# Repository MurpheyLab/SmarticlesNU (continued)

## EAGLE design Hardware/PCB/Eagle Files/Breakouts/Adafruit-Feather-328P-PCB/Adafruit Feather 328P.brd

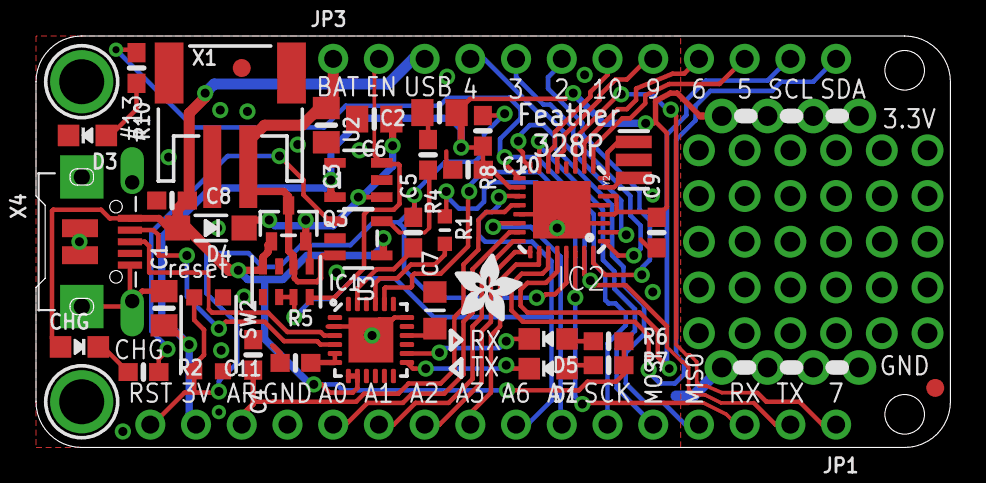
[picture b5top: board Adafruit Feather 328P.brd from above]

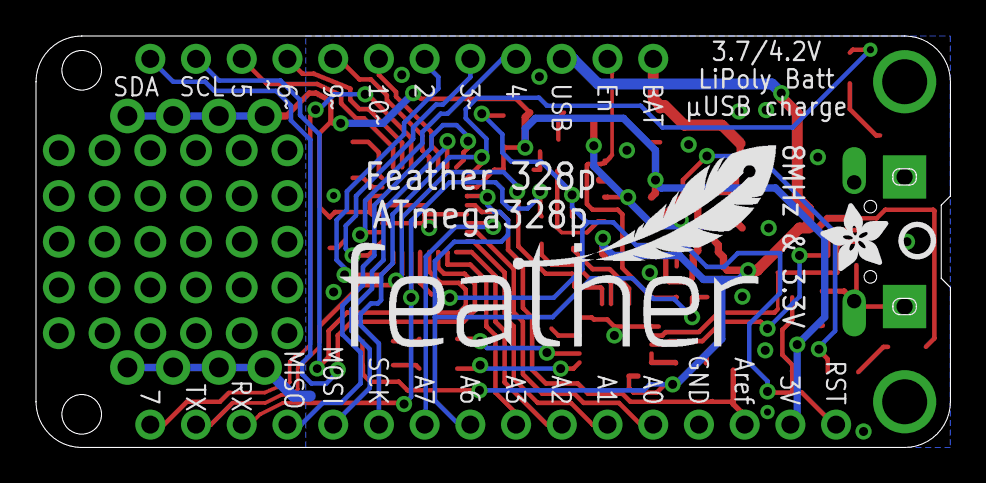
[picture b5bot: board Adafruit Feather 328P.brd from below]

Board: 2 copper layers, 50.8 x 22.9 mm, 43 parts (3 on the bottom side), 45 nets.

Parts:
C1, C2: 10uF; 0805-NO
C3, C6: 10µF; 0805-NO
C4, C5, C9, C10: 0.1uF; 0603-NO
C7: 10uF; _0805MP
C8, C11: 1uF; 0603-NO
CHG: ORANGE; CHIPLED_0805_NOOUTLINE
D1, D5: YELLOW; CHIPLED_0805_NOOUTLINE
D3: RED; CHIPLED_0805_NOOUTLINE
D4: MBR120; SOD-123
IC1: CP2104; QFN24_4MM_SMSC
IC2: ATMEGA328P; MLF32-TH
JP1: 1X16_ROUND
JP3: 1X12_ROUND
Q3: DMG341; SOT23-R
R1: 1K; _0603MP
R2, R6, R7, R10: 1K; 0603-NO
R4, R8: 10K; 0603-NO
R5: 100K; RESPACK_4X0603
SW2: KMR2; BTN_KMR2_4.6X2.8
U2: AP2112-3.3; SOT23-5
U3: MCP73831T-2ACI/OT; SOT23-5
U$9: FEATHERLOGO
U$13: PCBFEAT-REV-040
U$15, U$44: ADAFRUIT_3.5MM
U$31, U$32: MOUNTINGHOLE2.5; MOUNTINGHOLE_2.5_PLATED
U$34, U$35: FIDUCIAL_1MM
X1: JSTPH; JSTPH2
X4: 20329; 4UCONN_20329_V2
Y2: CSTCE16M0V53-R0 8MHZ; RESONATOR

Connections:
3.3V: C1.1, C2.1, C9.2, C10.2, IC2.4, IC2.6, IC2.18, JP1.15, R8.2, U2.5
A0: IC2.23, JP1.12
A1: IC2.24, JP1.11
A2: IC2.25, JP1.10
A3: IC2.26, JP1.9
A4/SDA: IC2.27, JP3.12
A5/SCL: IC2.28, JP3.11
A6: IC2.19, JP1.8, R5.6, R5.7
A7: IC2.22, JP1.7
AREF: C4.2, IC2.20, JP1.14
D0/RX: IC2.30, JP1.3, R1.1
D1/TX: IC1.20, IC2.31, JP1.2
D2: IC2.32, JP3.6
D3: IC2.1, JP3.5
D4: IC2.2, JP3.4
D5: IC2.9, JP3.10
D6: IC2.10, JP3.9
D7: IC2.11, JP1.1
D9: IC2.13, JP3.8
D10: IC2.14, JP3.7
D11/MOSI: IC2.15, JP1.5
D12/MISO: IC2.16, JP1.4
D13/SCK: IC2.17, JP1.6, R10.1
DTR: C5.1, IC1.23
EN: JP3.2, R5.8, U2.3
GND: C1.2, C2.2, C3.2, C4.1, C6.2, C7.2, C8.1, C9.1, C10.1, C11.2, D3.C, IC1.2, IC1.18, IC1.THERM, IC2.3, IC2.5, IC2.21, IC2.TH, JP1.13, R4.1, R5.3, R5.5, SW2.A, SW2.A', U2.2, U3.2, X1.1, X4.BASE@1, X4.BASE@2, X4.GND, X4.SPRT@1, X4.SPRT@2, X4.SPRT@3, X4.SPRT@4, Y2.2
unnamed: CHG.C, R2.1
unnamed: IC1.3, X4.D+
unnamed: R2.2, U3.1
unnamed: R4.2, U3.5
unnamed: D3.A, R10.2
unnamed: IC1.4, X4.D-
unnamed: C6.1, D4.C, Q3.2, R5.1, U2.1
unnamed: D1.A, R7.1
unnamed: D5.A, R6.1
unnamed: C11.1, IC1.5, IC1.6
unnamed: C7.1, IC1.16
RESET: C5.2, IC2.29, JP1.16, R8.1, SW2.B, SW2.B'
RXD: IC1.21, R1.2
RXLED: D1.C, IC1.13
TXLED: D5.C, IC1.14
VBAT: C3.1, JP3.1, Q3.3, R5.2, U3.3, X1.2
VBUS: C8.2, CHG.A, D4.A, IC1.7, IC1.8, JP3.3, Q3.1, R5.4, R6.2, R7.2, U3.4, X4.VBUS
XTAL1: IC2.8, Y2.3
XTAL2: IC2.7, Y2.1

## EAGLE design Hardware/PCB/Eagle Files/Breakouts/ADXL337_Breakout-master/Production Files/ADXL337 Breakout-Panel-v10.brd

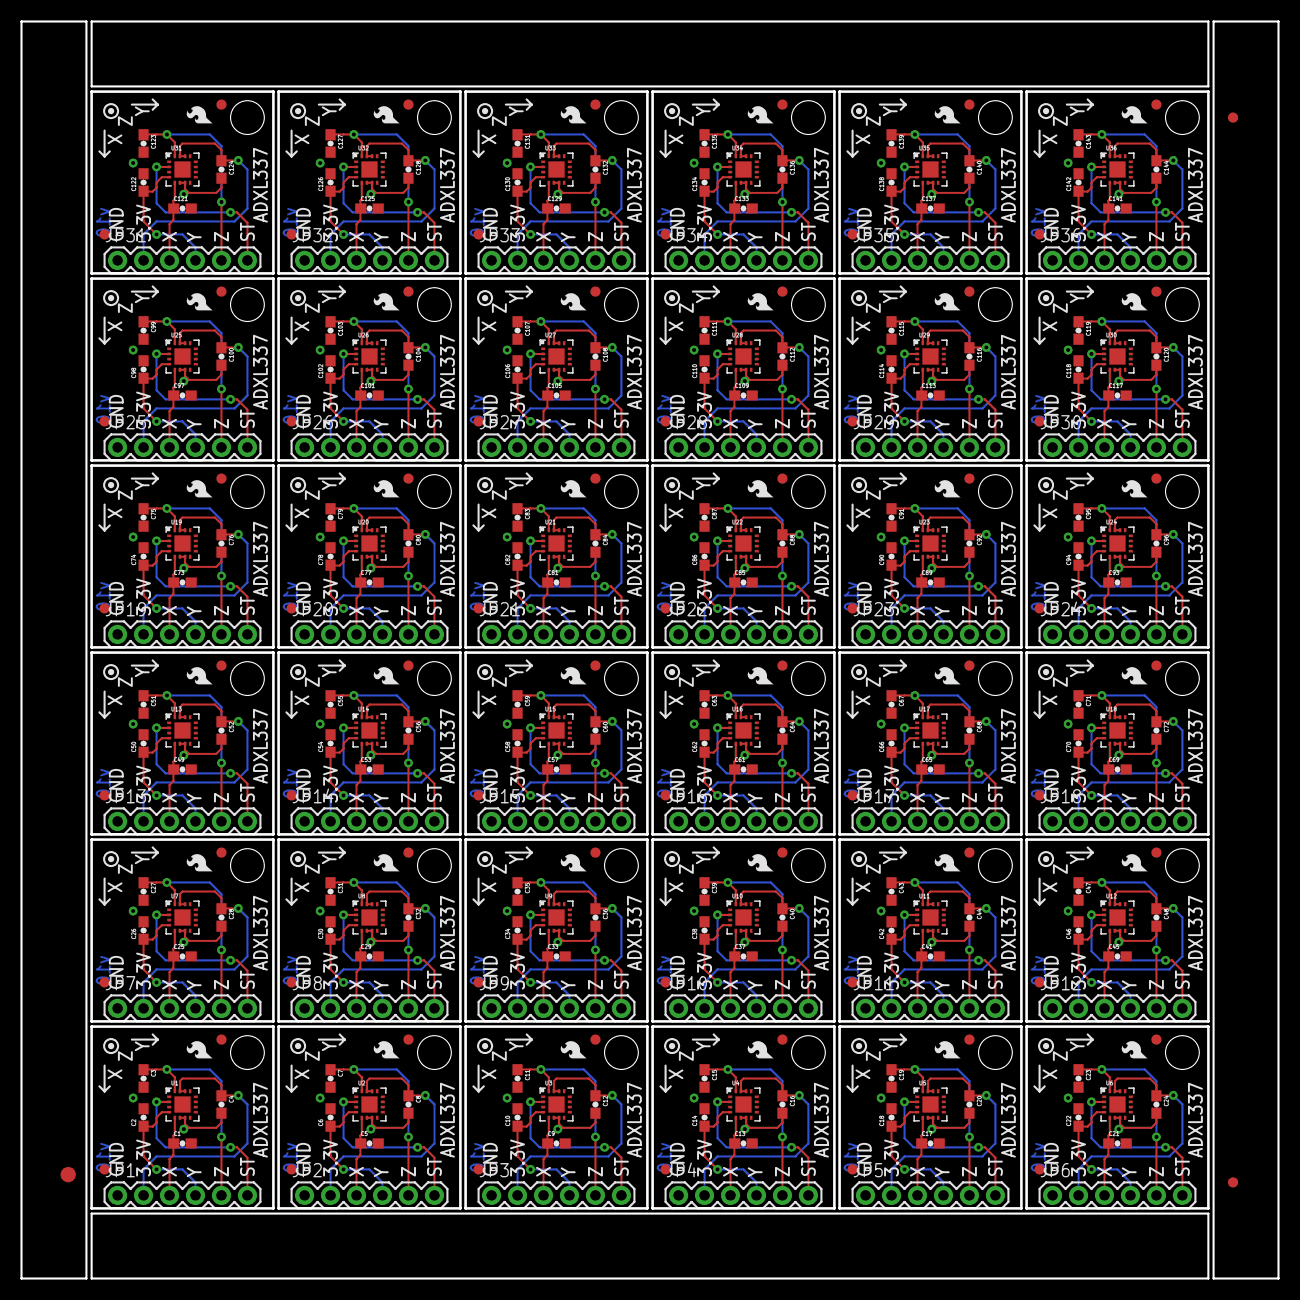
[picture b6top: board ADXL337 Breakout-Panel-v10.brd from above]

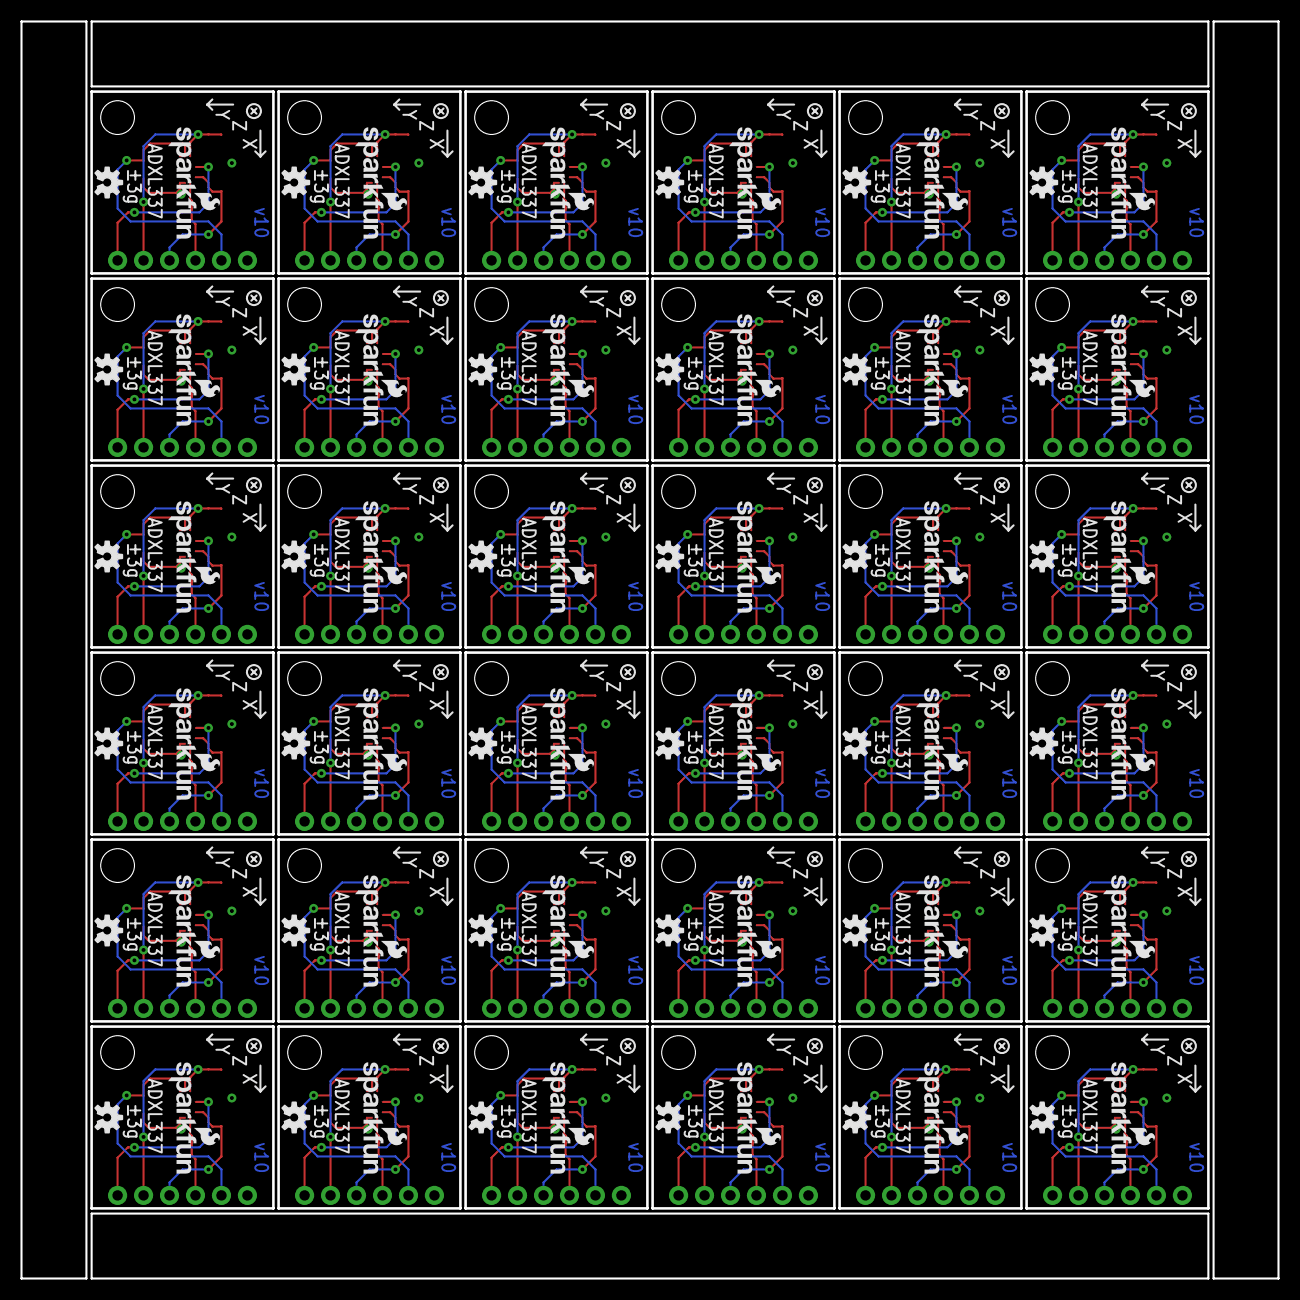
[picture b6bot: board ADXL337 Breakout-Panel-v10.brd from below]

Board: 2 copper layers, 122.9 x 122.9 mm, 435 parts (72 on the bottom side), 216 nets.

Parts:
C1, C2, C3, C5, C6, C7, C9, C10, C11, C13, C14, C15, C17, C18, C19, C21, C22, C23, C25, C26, C27, C29, C30, C31, C33, C34, C35, C37, C38, C39, C41, C42, C43, C45, C46, C47, C49, C50, C51, C53, C54, C55, C57, C58, C59, C61, C62, C63, C65, C66, C67, C69, C70, C71, C73, C74, C75, C77, C78, C79, C81, C82, C83, C85, C86, C87, C89, C90, C91, C93, C94, C95, C97, C98, C99, C101, C102, C103, C105, C106, C107, C109, C110, C111, C113, C114, C115, C117, C118, C119, C121, C122, C123, C125, C126, C127, C129, C130, C131, C133, C134, C135, C137, C138, C139, C141, C142, C143: 10nF; 0603-CAP
C4, C8, C12, C16, C20, C24, C28, C32, C36, C40, C44, C48, C52, C56, C60, C64, C68, C72, C76, C80, C84, C88, C92, C96, C100, C104, C108, C112, C116, C120, C124, C128, C132, C136, C140, C144: 0.1uF; 0603-CAP
E$1: FIDUCIAL-1.5X3
E$4, E$6: FIDUCIAL-1X2
FID1, FID2, FID3, FID4, FID5, FID6, FID7, FID8, FID9, FID10, FID11, FID12, FID13, FID14, FID15, FID16, FID17, FID18, FID19, FID20, FID21, FID22, FID23, FID24, FID25, FID26, FID27, FID28, FID29, FID30, FID31, FID32, FID33, FID34, FID35, FID36, FID37, FID38, FID39, FID40, FID41, FID42, FID43, FID44, FID45, FID46, FID47, FID48, FID49, FID50, FID51, FID52, FID53, FID54, FID55, FID56, FID57, FID58, FID59, FID60, FID61, FID62, FID63, FID64, FID65, FID66, FID67, FID68, FID69, FID70, FID71, FID72: FIDUCIAL1X2; FIDUCIAL-1X2
JP1, JP2, JP3, JP4, JP5, JP6, JP7, JP8, JP9, JP10, JP11, JP12, JP13, JP14, JP15, JP16, JP17, JP18, JP19, JP20, JP21, JP22, JP23, JP24, JP25, JP26, JP27, JP28, JP29, JP30, JP31, JP32, JP33, JP34, JP35, JP36: 1X06
LOGO1, LOGO4, LOGO7, LOGO10, LOGO13, LOGO16, LOGO19, LOGO22, LOGO25, LOGO28, LOGO31, LOGO34, LOGO37, LOGO40, LOGO43, LOGO46, LOGO49, LOGO52, LOGO55, LOGO58, LOGO61, LOGO64, LOGO67, LOGO70, LOGO73, LOGO76, LOGO79, LOGO82, LOGO85, LOGO88, LOGO91, LOGO94, LOGO97, LOGO100, LOGO103, LOGO106: SFE_LOGO_FLAME.1_INCH; SFE_LOGO_FLAME_.1
LOGO2, LOGO5, LOGO8, LOGO11, LOGO14, LOGO17, LOGO20, LOGO23, LOGO26, LOGO29, LOGO32, LOGO35, LOGO38, LOGO41, LOGO44, LOGO47, LOGO50, LOGO53, LOGO56, LOGO59, LOGO62, LOGO65, LOGO68, LOGO71, LOGO74, LOGO77, LOGO80, LOGO83, LOGO86, LOGO89, LOGO92, LOGO95, LOGO98, LOGO101, LOGO104, LOGO107: OSHW-LOGOS; OSHW-LOGO-S
LOGO3, LOGO6, LOGO9, LOGO12, LOGO15, LOGO18, LOGO21, LOGO24, LOGO27, LOGO30, LOGO33, LOGO36, LOGO39, LOGO42, LOGO45, LOGO48, LOGO51, LOGO54, LOGO57, LOGO60, LOGO63, LOGO66, LOGO69, LOGO72, LOGO75, LOGO78, LOGO81, LOGO84, LOGO87, LOGO90, LOGO93, LOGO96, LOGO99, LOGO102, LOGO105, LOGO108: SFE_LOGO_NAME_FLAME.1_INCH; SFE_LOGO_NAME_FLAME_.1
STANDOFF1, STANDOFF2, STANDOFF3, STANDOFF4, STANDOFF5, STANDOFF6, STANDOFF7, STANDOFF8, STANDOFF9, STANDOFF10, STANDOFF11, STANDOFF12, STANDOFF13, STANDOFF14, STANDOFF15, STANDOFF16, STANDOFF17, STANDOFF18, STANDOFF19, STANDOFF20, STANDOFF21, STANDOFF22, STANDOFF23, STANDOFF24, STANDOFF25, STANDOFF26, STANDOFF27, STANDOFF28, STANDOFF29, STANDOFF30, STANDOFF31, STANDOFF32, STANDOFF33, STANDOFF34, STANDOFF35, STANDOFF36: STAND-OFF
U1, U2, U3, U4, U5, U6, U7, U8, U9, U10, U11, U12, U13, U14, U15, U16, U17, U18, U19, U20, U21, U22, U23, U24, U25, U26, U27, U28, U29, U30, U31, U32, U33, U34, U35, U36: ADXL337; LFCSP_LQ-16

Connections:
3.3V: C4.1, JP1.2, U1.14, U1.15
3.3V1: C8.1, JP2.2, U2.14, U2.15
3.3V2: C12.1, JP3.2, U3.14, U3.15
3.3V3: C16.1, JP4.2, U4.14, U4.15
3.3V4: C20.1, JP5.2, U5.14, U5.15
3.3V5: C24.1, JP6.2, U6.14, U6.15
3.3V6: C28.1, JP7.2, U7.14, U7.15
3.3V7: C32.1, JP8.2, U8.14, U8.15
3.3V8: C36.1, JP9.2, U9.14, U9.15
3.3V9: C40.1, JP10.2, U10.14, U10.15
3.3V10: C44.1, JP11.2, U11.14, U11.15
3.3V11: C48.1, JP12.2, U12.14, U12.15
3.3V12: C52.1, JP13.2, U13.14, U13.15
3.3V13: C56.1, JP14.2, U14.14, U14.15
3.3V14: C60.1, JP15.2, U15.14, U15.15
3.3V15: C64.1, JP16.2, U16.14, U16.15
3.3V16: C68.1, JP17.2, U17.14, U17.15
3.3V17: C72.1, JP18.2, U18.14, U18.15
3.3V18: C76.1, JP19.2, U19.14, U19.15
3.3V19: C80.1, JP20.2, U20.14, U20.15
3.3V20: C84.1, JP21.2, U21.14, U21.15
3.3V21: C88.1, JP22.2, U22.14, U22.15
3.3V22: C92.1, JP23.2, U23.14, U23.15
3.3V23: C96.1, JP24.2, U24.14, U24.15
3.3V24: C100.1, JP25.2, U25.14, U25.15
3.3V25: C104.1, JP26.2, U26.14, U26.15
3.3V26: C108.1, JP27.2, U27.14, U27.15
3.3V27: C112.1, JP28.2, U28.14, U28.15
3.3V28: C116.1, JP29.2, U29.14, U29.15
3.3V29: C120.1, JP30.2, U30.14, U30.15
3.3V30: C124.1, JP31.2, U31.14, U31.15
3.3V31: C128.1, JP32.2, U32.14, U32.15
3.3V32: C132.1, JP33.2, U33.14, U33.15
3.3V33: C136.1, JP34.2, U34.14, U34.15
3.3V34: C140.1, JP35.2, U35.14, U35.15
3.3V35: C144.1, JP36.2, U36.14, U36.15
GND: C1.2, C2.2, C3.2, C4.2, JP1.1, U1.6, U1.7
GND1: C5.2, C6.2, C7.2, C8.2, JP2.1, U2.6, U2.7
GND2: C9.2, C10.2, C11.2, C12.2, JP3.1, U3.6, U3.7
GND3: C13.2, C14.2, C15.2, C16.2, JP4.1, U4.6, U4.7
GND4: C17.2, C18.2, C19.2, C20.2, JP5.1, U5.6, U5.7
GND5: C21.2, C22.2, C23.2, C24.2, JP6.1, U6.6, U6.7
GND6: C25.2, C26.2, C27.2, C28.2, JP7.1, U7.6, U7.7
GND7: C29.2, C30.2, C31.2, C32.2, JP8.1, U8.6, U8.7
GND8: C33.2, C34.2, C35.2, C36.2, JP9.1, U9.6, U9.7
GND9: C37.2, C38.2, C39.2, C40.2, JP10.1, U10.6, U10.7
GND10: C41.2, C42.2, C43.2, C44.2, JP11.1, U11.6, U11.7
GND11: C45.2, C46.2, C47.2, C48.2, JP12.1, U12.6, U12.7
GND12: C49.2, C50.2, C51.2, C52.2, JP13.1, U13.6, U13.7
GND13: C53.2, C54.2, C55.2, C56.2, JP14.1, U14.6, U14.7
GND14: C57.2, C58.2, C59.2, C60.2, JP15.1, U15.6, U15.7
GND15: C61.2, C62.2, C63.2, C64.2, JP16.1, U16.6, U16.7
GND16: C65.2, C66.2, C67.2, C68.2, JP17.1, U17.6, U17.7
GND17: C69.2, C70.2, C71.2, C72.2, JP18.1, U18.6, U18.7
GND18: C73.2, C74.2, C75.2, C76.2, JP19.1, U19.6, U19.7
GND19: C77.2, C78.2, C79.2, C80.2, JP20.1, U20.6, U20.7
GND20: C81.2, C82.2, C83.2, C84.2, JP21.1, U21.6, U21.7
GND21: C85.2, C86.2, C87.2, C88.2, JP22.1, U22.6, U22.7
GND22: C89.2, C90.2, C91.2, C92.2, JP23.1, U23.6, U23.7
GND23: C93.2, C94.2, C95.2, C96.2, JP24.1, U24.6, U24.7
GND24: C97.2, C98.2, C99.2, C100.2, JP25.1, U25.6, U25.7
GND25: C101.2, C102.2, C103.2, C104.2, JP26.1, U26.6, U26.7
GND26: C105.2, C106.2, C107.2, C108.2, JP27.1, U27.6, U27.7
GND27: C109.2, C110.2, C111.2, C112.2, JP28.1, U28.6, U28.7
GND28: C113.2, C114.2, C115.2, C116.2, JP29.1, U29.6, U29.7
GND29: C117.2, C118.2, C119.2, C120.2, JP30.1, U30.6, U30.7
GND30: C121.2, C122.2, C123.2, C124.2, JP31.1, U31.6, U31.7
GND31: C125.2, C126.2, C127.2, C128.2, JP32.1, U32.6, U32.7
GND32: C129.2, C130.2, C131.2, C132.2, JP33.1, U33.6, U33.7
GND33: C133.2, C134.2, C135.2, C136.2, JP34.1, U34.6, U34.7
GND34: C137.2, C138.2, C139.2, C140.2, JP35.1, U35.6, U35.7
GND35: C141.2, C142.2, C143.2, C144.2, JP36.1, U36.6, U36.7
ST: JP1.6, U1.2
ST1: JP2.6, U2.2
ST2: JP3.6, U3.2
ST3: JP4.6, U4.2
ST4: JP5.6, U5.2
ST5: JP6.6, U6.2
ST6: JP7.6, U7.2
ST7: JP8.6, U8.2
ST8: JP9.6, U9.2
ST9: JP10.6, U10.2
ST10: JP11.6, U11.2
ST11: JP12.6, U12.2
ST12: JP13.6, U13.2
ST13: JP14.6, U14.2
ST14: JP15.6, U15.2
ST15: JP16.6, U16.2
ST16: JP17.6, U17.2
ST17: JP18.6, U18.2
ST18: JP19.6, U19.2
ST19: JP20.6, U20.2
ST20: JP21.6, U21.2
ST21: JP22.6, U22.2
ST22: JP23.6, U23.2
ST23: JP24.6, U24.2
ST24: JP25.6, U25.2
ST25: JP26.6, U26.2
ST26: JP27.6, U27.2
ST27: JP28.6, U28.2
ST28: JP29.6, U29.2
ST29: JP30.6, U30.2
ST30: JP31.6, U31.2
ST31: JP32.6, U32.2
ST32: JP33.6, U33.2
ST33: JP34.6, U34.2
ST34: JP35.6, U35.2
ST35: JP36.6, U36.2
X: C1.1, JP1.3, U1.5
X1: C5.1, JP2.3, U2.5
X2: C9.1, JP3.3, U3.5
X3: C13.1, JP4.3, U4.5
X4: C17.1, JP5.3, U5.5
X5: C21.1, JP6.3, U6.5
X6: C25.1, JP7.3, U7.5
X7: C29.1, JP8.3, U8.5
X8: C33.1, JP9.3, U9.5
X9: C37.1, JP10.3, U10.5
X10: C41.1, JP11.3, U11.5
X11: C45.1, JP12.3, U12.5
X12: C49.1, JP13.3, U13.5
X13: C53.1, JP14.3, U14.5
X14: C57.1, JP15.3, U15.5
X15: C61.1, JP16.3, U16.5
X16: C65.1, JP17.3, U17.5
X17: C69.1, JP18.3, U18.5
X18: C73.1, JP19.3, U19.5
X19: C77.1, JP20.3, U20.5
X20: C81.1, JP21.3, U21.5
X21: C85.1, JP22.3, U22.5
X22: C89.1, JP23.3, U23.5
X23: C93.1, JP24.3, U24.5
X24: C97.1, JP25.3, U25.5
X25: C101.1, JP26.3, U26.5
X26: C105.1, JP27.3, U27.5
X27: C109.1, JP28.3, U28.5
X28: C113.1, JP29.3, U29.5
X29: C117.1, JP30.3, U30.5
X30: C121.1, JP31.3, U31.5
X31: C125.1, JP32.3, U32.5
X32: C129.1, JP33.3, U33.5
X33: C133.1, JP34.3, U34.5
X34: C137.1, JP35.3, U35.5
X35: C141.1, JP36.3, U36.5
Y: C2.1, JP1.4, U1.4
Y1: C6.1, JP2.4, U2.4
Y2: C10.1, JP3.4, U3.4
Y3: C14.1, JP4.4, U4.4
Y4: C18.1, JP5.4, U5.4
Y5: C22.1, JP6.4, U6.4
Y6: C26.1, JP7.4, U7.4
Y7: C30.1, JP8.4, U8.4
Y8: C34.1, JP9.4, U9.4
Y9: C38.1, JP10.4, U10.4
Y10: C42.1, JP11.4, U11.4
Y11: C46.1, JP12.4, U12.4
Y12: C50.1, JP13.4, U13.4
Y13: C54.1, JP14.4, U14.4
Y14: C58.1, JP15.4, U15.4
Y15: C62.1, JP16.4, U16.4
Y16: C66.1, JP17.4, U17.4
Y17: C70.1, JP18.4, U18.4
Y18: C74.1, JP19.4, U19.4
Y19: C78.1, JP20.4, U20.4
Y20: C82.1, JP21.4, U21.4
Y21: C86.1, JP22.4, U22.4
Y22: C90.1, JP23.4, U23.4
Y23: C94.1, JP24.4, U24.4
Y24: C98.1, JP25.4, U25.4
Y25: C102.1, JP26.4, U26.4
Y26: C106.1, JP27.4, U27.4
Y27: C110.1, JP28.4, U28.4
Y28: C114.1, JP29.4, U29.4
Y29: C118.1, JP30.4, U30.4
Y30: C122.1, JP31.4, U31.4
Y31: C126.1, JP32.4, U32.4
Y32: C130.1, JP33.4, U33.4
Y33: C134.1, JP34.4, U34.4
Y34: C138.1, JP35.4, U35.4
Y35: C142.1, JP36.4, U36.4
Z: C3.1, JP1.5, U1.16
Z1: C7.1, JP2.5, U2.16
Z2: C11.1, JP3.5, U3.16
Z3: C15.1, JP4.5, U4.16
Z4: C19.1, JP5.5, U5.16
Z5: C23.1, JP6.5, U6.16
Z6: C27.1, JP7.5, U7.16
Z7: C31.1, JP8.5, U8.16
Z8: C35.1, JP9.5, U9.16
Z9: C39.1, JP10.5, U10.16
Z10: C43.1, JP11.5, U11.16
Z11: C47.1, JP12.5, U12.16
Z12: C51.1, JP13.5, U13.16
Z13: C55.1, JP14.5, U14.16
Z14: C59.1, JP15.5, U15.16
Z15: C63.1, JP16.5, U16.16
Z16: C67.1, JP17.5, U17.16
Z17: C71.1, JP18.5, U18.16
Z18: C75.1, JP19.5, U19.16
Z19: C79.1, JP20.5, U20.16
Z20: C83.1, JP21.5, U21.16
Z21: C87.1, JP22.5, U22.16
Z22: C91.1, JP23.5, U23.16
Z23: C95.1, JP24.5, U24.16
Z24: C99.1, JP25.5, U25.16
Z25: C103.1, JP26.5, U26.16
Z26: C107.1, JP27.5, U27.16
Z27: C111.1, JP28.5, U28.16
Z28: C115.1, JP29.5, U29.16
Z29: C119.1, JP30.5, U30.16
Z30: C123.1, JP31.5, U31.16
Z31: C127.1, JP32.5, U32.16
Z32: C131.1, JP33.5, U33.16
Z33: C135.1, JP34.5, U34.16
Z34: C139.1, JP35.5, U35.16
Z35: C143.1, JP36.5, U36.16

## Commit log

2019-08-19 release v1.0
2019-08-19 cpp Doc
    added some documentation to .cpp files. Still needs more
2019-08-19 added. ino code
2019-08-19 fixed typo
2019-08-19 reorganized files
2019-08-29 stable release?
2019-08-30 renamed example file
2019-08-30 comments
2019-08-30 added arduino Libraries
2019-08-30 organization changes
2019-08-30 purge
2019-08-30 indent
2019-08-30 stream servo cpp work
2019-08-31 Added folders to ignore when using Jupyter notebooks
2019-09-10 stream servo work
2019-09-10 debug work
2019-09-10 add square gait example file
2019-09-10 update params
2019-09-10 comment out debug messages
2019-09-10 sync ex uses square gait
2019-09-11 change init mode
    This commit changes init_mode() so that only changing to IDLE resests all flags (_transmit, _read_sensors, _run_servos, etc.) Before this happened whenever a mode change occurred. However, for upcomi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
    Additionally, this commit changes init_mode so that _gaitL and _gaitR are not reset to default values when switching into the INTERP mode, only when switching into the IDLE mode.
2019-09-11 Update Smarticle.cpp
    Deleted blocking while statement in rx_interrupt. Not sure how this will work as the interrupt tries to read something main() is writing to
2019-09-11 Update Smarticle.h
    fixed bug
2019-09-11 rename StreamServo -> StreamServoThread
2019-09-11 rename module
2019-09-11 example file
2019-09-11 fix programmable smarticle
2019-09-11 rename example
2019-09-11 fixed rx bug
2019-09-12 rename to StreamThread and change implementation to be subclass of Thread
2019-09-12 change calls to StreamThread rather than old StreamServo
2019-09-13 added functions
    added go_to_stream() and go_to_gi() functions in exampe
2019-09-13 Update StreamThread
    changed thread_flag to run_flag
    changed broadcast to command
    fixed bytearray bug
2019-09-13 buffer
    added 3 message buffer system as well as changed way messages are handled with manage_msg() function
2019-09-13 stream work
    things are kinda broken now; deleted _run_servos flag and just have enable/disable interrupts. We'll see if this is a good idea lol
2019-09-16 stream servo example
    change rx callback to not decode messages
2019-09-16 build_network changes
    add xbee buffer purge and delay to end of build_network()
2019-09-16 reliability fix
    1) eliminiated _input_string and just made increased dimension of _input_msg; removes need for time_intensive str_copy
    2) added _debug functionality
    3) fixed bug where buffer would overflow when streaming and then set_mode to IDLE
2019-09-16 Smarticle Class work
    change class initialization; delete cycle_time_ms; delete set_servos function >>replaced by enable/disable t4_interrupts; allow different random streamed poses
2019-09-16 unique random streams
2019-09-16 streaming functionality
    added functionality for unique random gaits and also unique random corner gaits
2019-09-16 fix bugs
    fix random numbers end number is not inclusive; fix gait interpolate
2019-09-16 Update programmable_smarticle.ino
    don't use debug
2019-09-16 randomSeed
    use randomSeed to make the random numbers unique
2019-09-16 Update SmarticleStreamServoExample.py
    use random corners
2019-09-17 random seed change
2019-09-17 remove mac os files
2019-09-17 Update .gitignore
    remove mac unique files from everywhere
2019-09-17 Removing yet more of the mac files
2019-09-17 Fixed some weird typos that popped up in the merge
2019-09-18 random stream delay
    option to set delay after command is received so that smarticles getting streamed commands are not in sync. Also changed attach_servos() so that it will only execute when servos are detached.
2019-09-18 repo work
2019-09-18 random delay in streaming
2019-09-18 stream servo delay work
2019-09-18 Update SmarticleSwarm.py
    remove min_val for random delay
2019-09-27 int to bool and gi t0 gait_init
2019-10-29 updated examples
2019-10-31 change software serial to hardware serial
2019-11-01 v2 updates
    changed software serial to hardware serial
    updated pins for sensors and servos
2019-11-01 NeoHWSerial
2019-11-21 bug fixes + single pose streaming
    fixed bug of multiple devices printing. Added simple stream functionality with example
2019-11-22 make changes to get to work on SmarticleMainframe
2019-11-23 fixed printing issues
    changed debug to default to zero and will automatically print discovery messages
2019-11-25 debug smarticle ID names and add Queue Streaming to enable sending actions in real time
2019-11-25 changed examples for Linux USB port names
2019-11-26 add asynchrronous sending capabilities
2019-11-26 fixed queue streaming
2019-12-03 make changes to random gaits and streams
2019-12-04 fixed plank synchronization bug
2019-12-04 Added Queue plank file
2019-12-04 changes to import statements for random gaits example
2019-12-04 update action queue function
    added function for updating action queue using action vector format from our RL side
2019-12-05 fix plank issues
2019-12-05 rename asynck
2019-12-09 sync noise and pose noise
2019-12-09 noise on square gait
2019-12-09 gait interp plank bug
2019-12-10 pose noise bug fix
2019-12-10 fixed pose_noise bug
2019-12-10 pose noise fix
2019-12-11 fixed pose noise bug
2019-12-11 update sync thread
    changed sync period to match gait period and added sync time list
2020-01-14 update transmit data
2020-01-15 light plank python side
2020-01-15 light_plank cpp side
2020-01-15 light_plank work
    deleted separate mode for light plank
2020-01-15 light palnk work cpp
2020-01-15 ligh plank features
2020-01-19 pose epsilon
    allow robot to execute action with (1-epsilon probability)
2020-01-19 pose epsilon capabilities
2020-01-20 change to random corners
    also fix bug so that angR is written to right servo
2020-01-20 change to random corners for pose_epsilon
2020-01-31 documentation
2020-02-03 add functionality for switching between gaits
2020-02-03 smarticle code for gait select functionality
2020-02-03 gat select example
2020-02-03 add gait select capability
2020-02-13 add testing script
2020-02-13 skeleton of new interp msg function
2020-02-13 everything is in disarray -- will pick up here tomorrow
2020-02-13 no syntax errors woot!!
2020-02-14 MESSAGE SYSTEM WORKING
2020-02-14 example that shows performance
2020-06-17 changes to transmitting data
2020-06-17 rename asynk to asynch
2020-06-17 rename folder to pysmarticle
2020-06-19 allow for editable transmit counts
2020-06-19 work on new servo stream
2020-06-19 moved set_transmit_counts
2020-06-19 fix set_pose
2020-06-19 finish new streaming and plank commands
2020-06-23 name package pysmarticle
2020-06-24 description header
2020-06-24 add hardware files
2020-09-25 psuedo env built for testing
2020-09-25 import change for python 3.8
2020-09-25 example test changes
2020-09-25 fix integer problem
2020-09-25 TEST
2020-10-21 CAM zip files
2020-10-21 pcbway params
